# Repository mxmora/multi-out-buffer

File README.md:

# multi-out-buffer

This circuit was based on the buffer circuit from <http://www.muzique.com/lab/splitter.htm> ©2007 Jack Orman All Rights Reserved

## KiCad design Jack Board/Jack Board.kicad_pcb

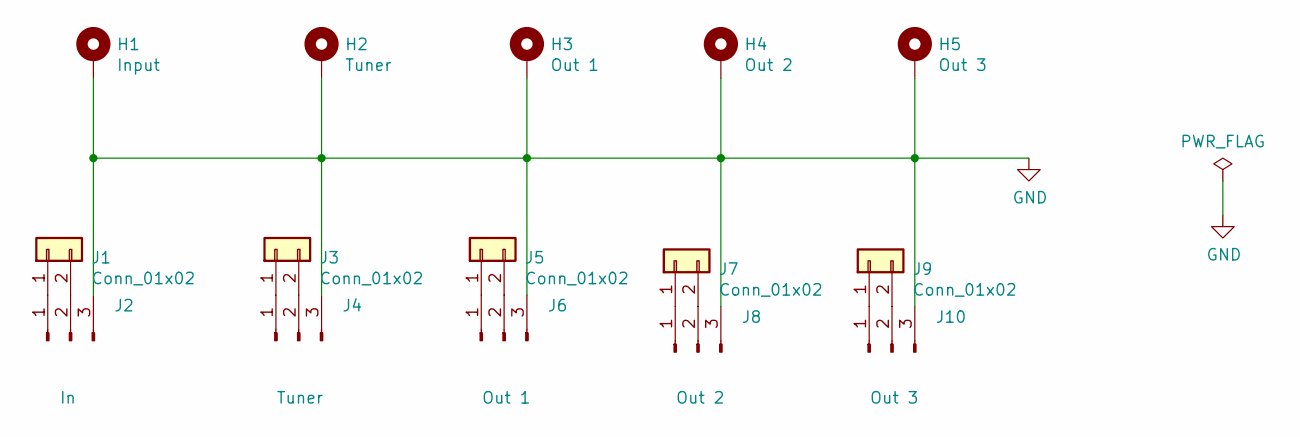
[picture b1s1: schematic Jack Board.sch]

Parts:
H1: Input; MountingHole_6.4mm_M6_Pad
H2: Tuner; MountingHole_6.4mm_M6_Pad
H3: Out 1; MountingHole_6.4mm_M6_Pad
H4: Out 2; MountingHole_6.4mm_M6_Pad
H5: Out 3; MountingHole_6.4mm_M6_Pad
J1, J3, J5, J7, J9: Conn_01x02; PinHeader_1x02_P1.27mm_Vertical
J2: In; PinHeader_1x03_P1.27mm_Vertical
J4: Tuner; PinHeader_1x03_P1.27mm_Vertical
J6: Out 1; PinHeader_1x03_P1.27mm_Vertical
J8: Out 2; PinHeader_1x03_P1.27mm_Vertical
J10: Out 3; PinHeader_1x03_P1.27mm_Vertical

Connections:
GND: H1.1, H2.1, H3.1, H4.1, H5.1, J2.3, J4.3, J6.3, J8.3, J10.3
unnamed: J1.1, J2.1
unnamed: J1.2, J2.2
unnamed: J3.1, J4.1
unnamed: J3.2, J4.2
unnamed: J5.1, J6.1
unnamed: J5.2, J6.2
unnamed: J7.1, J8.1
unnamed: J7.2, J8.2
unnamed: J9.1, J10.1
unnamed: J9.2, J10.2

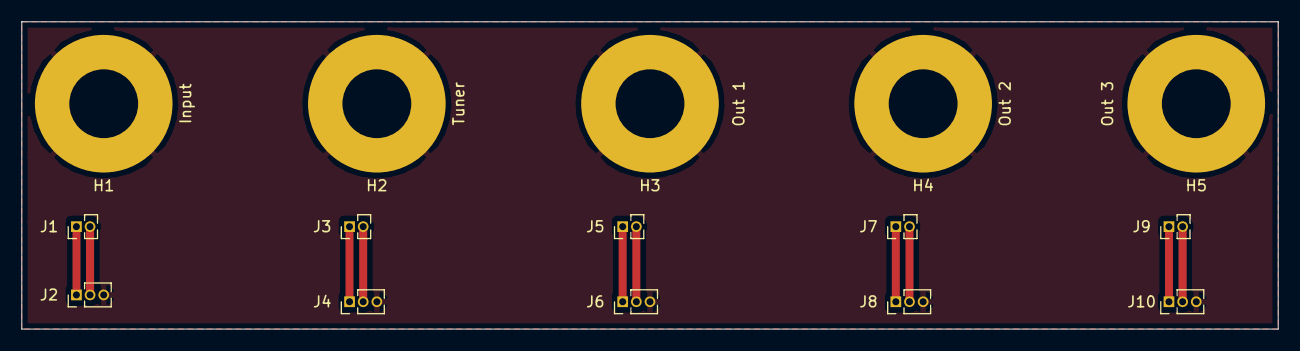
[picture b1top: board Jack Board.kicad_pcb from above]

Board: 2 copper layers, 116.8 x 28.6 mm, 15 parts (0 on the bottom side), 11 nets.

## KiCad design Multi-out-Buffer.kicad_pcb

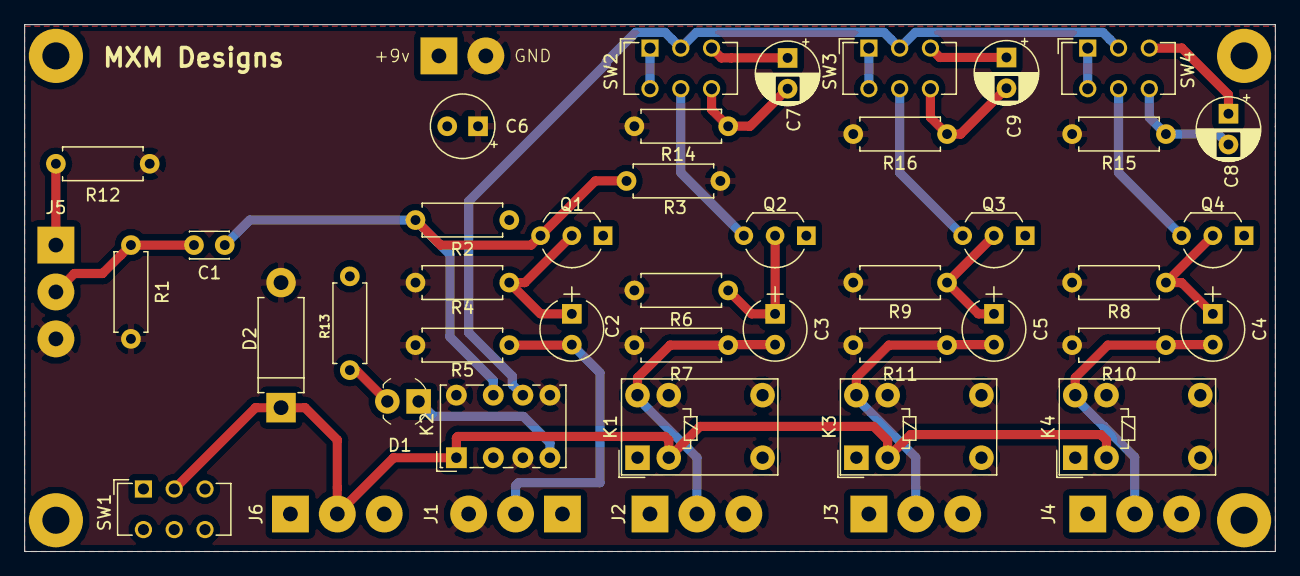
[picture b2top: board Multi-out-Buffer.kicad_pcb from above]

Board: 2 copper layers, 101.6 x 42.8 mm, 50 parts (0 on the bottom side), 29 nets.

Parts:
C1: 0.1; C_Disc_D3.0mm_W2.0mm_P2.50mm
C2, C3, C4, C5: 1uF; CP_Radial_Tantal_D5.0mm_P2.50mm
C6: 10F; CP_Radial_Tantal_D5.0mm_P2.50mm
C7, C8, C9: 10F; CP_Radial_D5.0mm_P2.50mm
D1: LED; LED_3mm_Radial
D2: SB120; D_DO-15_P10.16mm_Horizontal
J1: Out1; SolderWirePad_1x03_P3.81mm_Drill1.2mm
J2: Out2; SolderWirePad_1x03_P3.81mm_Drill1.2mm
J3: Out3; SolderWirePad_1x03_P3.81mm_Drill1.2mm
J4: Out4; SolderWirePad_1x03_P3.81mm_Drill1.2mm
J5: Input1; SolderWirePad_1x03_P3.81mm_Drill1.2mm
J6: FootSwitchJack; SolderWirePad_1x03_P3.81mm_Drill1.2mm
J7: PWR; SolderWirePad_1x02_P3.81mm_Drill1.2mm
J8, J8#2, J9, J9#2: Mechanical; MountingHole_2.2mm_M2_Pad
K1, K3, K4: G5V-1; Relay_SPDT_Omron_G5V-1
K2: G6K-2P; Relay_DPDT_Omron_G6K-2P-Y
Q1, Q2, Q3, Q4: MFPJ102; TO-92_Inline_Wide
R1: 10m; R_Axial_DIN0207_L6.3mm_D2.5mm_P7.62mm_Horizontal
R2, R3: 2.2M; R_Axial_DIN0207_L6.3mm_D2.5mm_P7.62mm_Horizontal
R4, R6, R8, R9: 10k; R_Axial_DIN0207_L6.3mm_D2.5mm_P7.62mm_Horizontal
R5, R7, R10, R11, R12: 100k; R_Axial_DIN0207_L6.3mm_D2.5mm_P7.62mm_Horizontal
R13: 680; R_Axial_DIN0207_L6.3mm_D2.5mm_P7.62mm_Horizontal
R14, R15, R16: 220; R_Axial_DIN0207_L6.3mm_D2.5mm_P7.62mm_Horizontal
SW1: SW_Tuner; SW_CuK_JS202011CQN_DPDT_Straight
SW2, SW3, SW4: SW_DPDT_x2; SW_CuK_JS202011CQN_DPDT_Straight

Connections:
+9V: C6.2, J6.1, J7.1, Q1.1, Q2.1, Q3.1, Q4.1, R2.1, R13.1, SW1.3
GND: C6.1, D2.2, J1.3, J2.3, J3.3, J4.3, J5.3, J7.2, K1.5, K1.6, K1.9, K2.3, K2.5, K2.8, K3.5, K3.6, K3.9, K4.5, K4.6, K4.9, R1.2, R3.2, R4.2, R5.2, R6.2, R7.2, R8.2, R9.2, R10.2, R11.2, R12.1, R14.2, R15.2, R16.2
unnamed: C1.1, K2.7, Q1.3, R2.2, R3.1
unnamed: C1.2, J5.2, R1.1
unnamed: C2.1, Q1.2, R4.1
unnamed: C2.2, J1.2, R5.1
unnamed: C3.1, Q2.2, R6.1
unnamed: C3.2, J2.2, K1.10, R7.1
unnamed: C4.1, Q4.2, R8.1
unnamed: C4.2, J4.2, K4.10, R10.1
unnamed: C5.1, Q3.2, R9.1
unnamed: C5.2, J3.2, K3.10, R11.1
unnamed: C7.1, SW2.3
unnamed: C7.2, R14.1, SW2.6
unnamed: C8.1, SW4.3
unnamed: C8.2, R15.1, SW4.6
unnamed: C9.1, SW3.3
unnamed: C9.2, R16.1, SW3.6
unnamed: D1.1, K2.4
unnamed: D1.2, R13.2
unnamed: D2.1, J6.2, K1.2, K2.1, K3.2, K4.2, SW1.2
unnamed: J5.1, R12.2
unnamed: K2.6, SW2.2, SW3.2, SW4.2
unnamed: Q2.3, SW2.5
unnamed: Q3.3, SW3.5
unnamed: Q4.3, SW4.5
unnamed: SW2.1, SW2.4
unnamed: SW3.1, SW3.4
unnamed: SW4.1, SW4.4

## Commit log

2019-04-04 add files
2019-04-04 add gerbers
2019-04-04 add connector
2019-04-04 new file
2019-04-04 add jack board
2019-04-04 Create LICENSE
2019-04-04 add attribution
2019-04-13 add preview files to better understand what version it is
